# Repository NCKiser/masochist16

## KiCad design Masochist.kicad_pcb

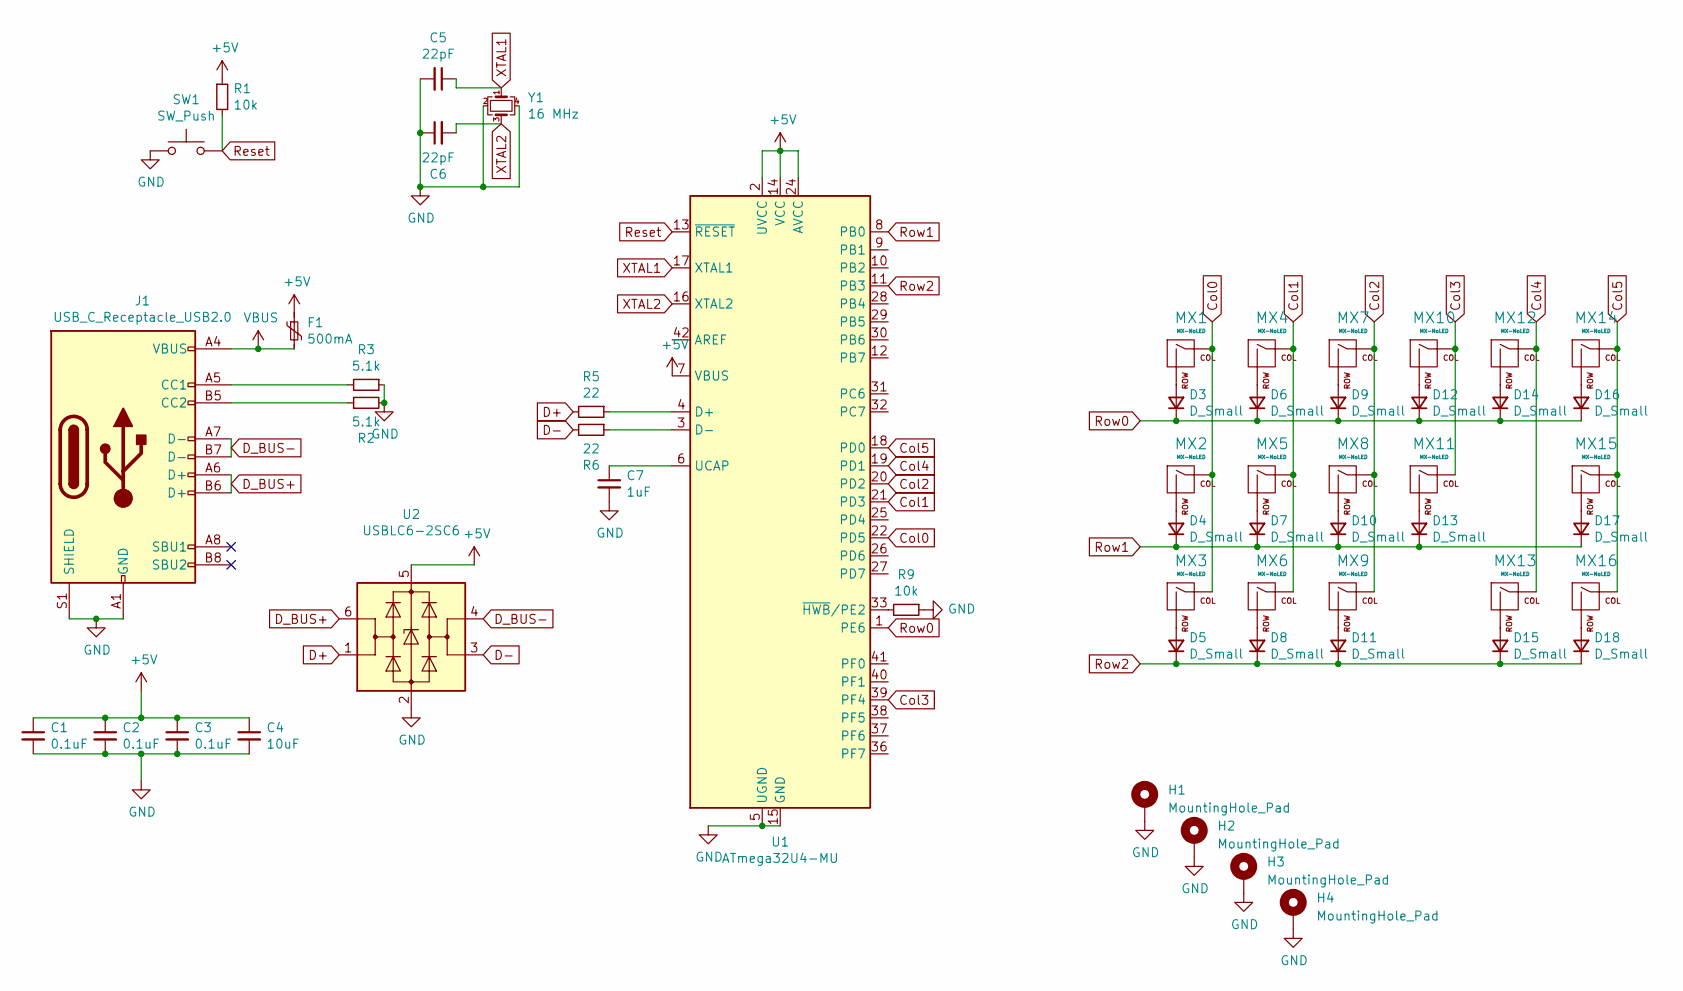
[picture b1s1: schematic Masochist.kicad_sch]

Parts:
C1, C2, C3: 0.1uF; C_0805_2012Metric
C4: 10uF; C_0805_2012Metric
C5, C6: 22pF; C_0805_2012Metric
C7: 1uF; C_0402_1005Metric
D3, D4, D5, D6, D7, D8, D9, D10, D11, D12, D13, D14, D15, D16, D17, D18: D_Small; D_SOD-123
F1: 500mA; Fuse_1206_3216Metric
H1, H2, H3, H4: MountingHole_Pad; MountingHole_2.2mm_M2_Pad
J1: USB_C_Receptacle_USB2.0; USB_C_Receptacle_XKB_U262-16XN-4BVC11
MX1, MX3, MX4, MX5, MX6, MX7, MX8, MX10, MX11, MX12, MX13, MX14, MX16: MX-NoLED; MXOnly-1U-NoLED
MX2: MX-NoLED; MXOnly-1.25U-NoLED
MX9: MX-NoLED; MXOnly-2U-ReversedStabilizers-NoLED
MX15: MX-NoLED; MXOnly-1.75U-NoLED
R1, R9: 10k; R_0805_2012Metric
R2, R3: 5.1k; R_0805_2012Metric
R5, R6: 22; R_0805_2012Metric
SW1: SW_Push; SKQG-1155865
U1: ATmega32U4-MU; QFN-44-1EP_7x7mm_P0.5mm_EP5.2x5.2mm
U2: USBLC6-2SC6; SOT-23-6
Y1: 16 MHz; Crystal_SMD_3225-4Pin_3.2x2.5mm

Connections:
+5V: C1.1, C2.1, C3.1, C4.1, F1.1, R1.1, U1.2 (UVCC), U1.7 (VBUS), U1.14 (VCC), U1.24 (AVCC), U1.34 (VCC), U1.44 (AVCC), U2.5 (VBUS)
Col0: MX1.1 (COL), MX2.1 (COL), MX3.1 (COL), U1.22 (PD5)
Col1: MX4.1 (COL), MX5.1 (COL), MX6.1 (COL), U1.21 (PD3)
Col2: MX7.1 (COL), MX8.1 (COL), MX9.1 (COL), U1.20 (PD2)
Col3: MX10.1 (COL), MX11.1 (COL), U1.39 (PF4)
Col4: MX12.1 (COL), MX13.1 (COL), U1.19 (PD1)
Col5: MX14.1 (COL), MX15.1 (COL), MX16.1 (COL), U1.18 (PD0)
D+: R5.2, U2.1 (I/O1)
D-: R6.2, U2.3 (I/O2)
D_BUS+: J1.A6 (D+), J1.B6 (D+), U2.6 (I/O1)
D_BUS-: J1.A7 (D-), J1.B7 (D-), U2.4 (I/O2)
GND: C1.2, C2.2, C3.2, C4.2, C5.2, C6.1, C7.2, H1.1, H2.1, H3.1, H4.1, J1.A1 (GND), J1.A12 (GND), J1.B1 (GND), J1.B12 (GND), J1.S1 (SHIELD), R2.2, R3.1, R9.1, SW1.1, U1.5 (UGND), U1.15 (GND), U1.23 (GND), U1.35 (GND), U1.43 (GND), U1.45 (GND), U2.2 (GND), Y1.2, Y1.4
unnamed: D3.2 (A), MX1.2 (ROW)
unnamed: D4.2 (A), MX2.2 (ROW)
unnamed: D5.2 (A), MX3.2 (ROW)
unnamed: D6.2 (A), MX4.2 (ROW)
unnamed: D7.2 (A), MX5.2 (ROW)
unnamed: D8.2 (A), MX6.2 (ROW)
unnamed: D9.2 (A), MX7.2 (ROW)
unnamed: D10.2 (A), MX8.2 (ROW)
unnamed: D11.2 (A), MX9.2 (ROW)
unnamed: D12.2 (A), MX10.2 (ROW)
unnamed: D13.2 (A), MX11.2 (ROW)
unnamed: D14.2 (A), MX12.2 (ROW)
unnamed: D15.2 (A), MX13.2 (ROW)
unnamed: D16.2 (A), MX14.2 (ROW)
unnamed: D17.2 (A), MX15.2 (ROW)
unnamed: D18.2 (A), MX16.2 (ROW)
unnamed: J1.A5 (CC1), R3.2
unnamed: J1.B5 (CC2), R2.1
unnamed: R5.1, U1.4 (D+)
unnamed: R6.1, U1.3 (D-)
unnamed: C7.1, U1.6 (UCAP)
unnamed: R9.2, U1.33 (~HWB/PE2)
Reset: R1.2, SW1.2, U1.13 (~RESET)
Row0: D3.1 (K), D6.1 (K), D9.1 (K), D12.1 (K), D14.1 (K), D16.1 (K), U1.1 (PE6)
Row1: D4.1 (K), D7.1 (K), D10.1 (K), D13.1 (K), D17.1 (K), U1.8 (PB0)
Row2: D5.1 (K), D8.1 (K), D11.1 (K), D15.1 (K), D18.1 (K), U1.11 (PB3)
VBUS: F1.2, J1.A4 (VBUS), J1.A9 (VBUS), J1.B4 (VBUS), J1.B9 (VBUS)
XTAL1: C5.1, U1.17 (XTAL1), Y1.1
XTAL2: C6.2, U1.16 (XTAL2), Y1.3

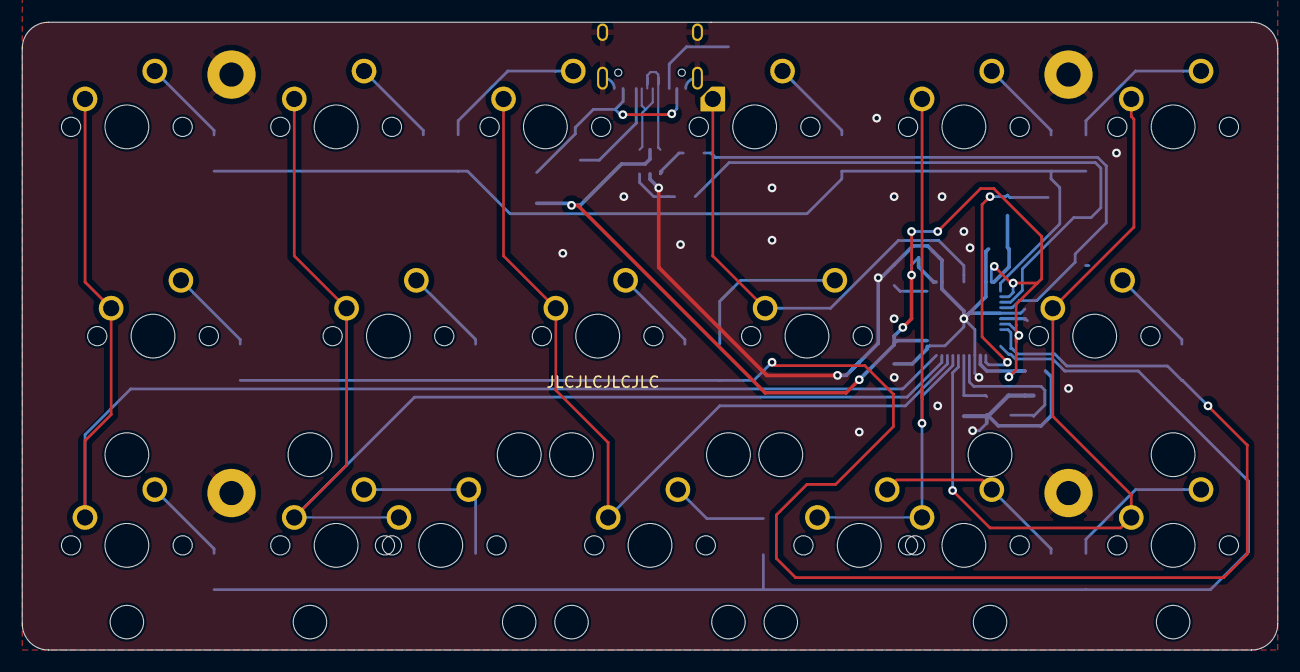
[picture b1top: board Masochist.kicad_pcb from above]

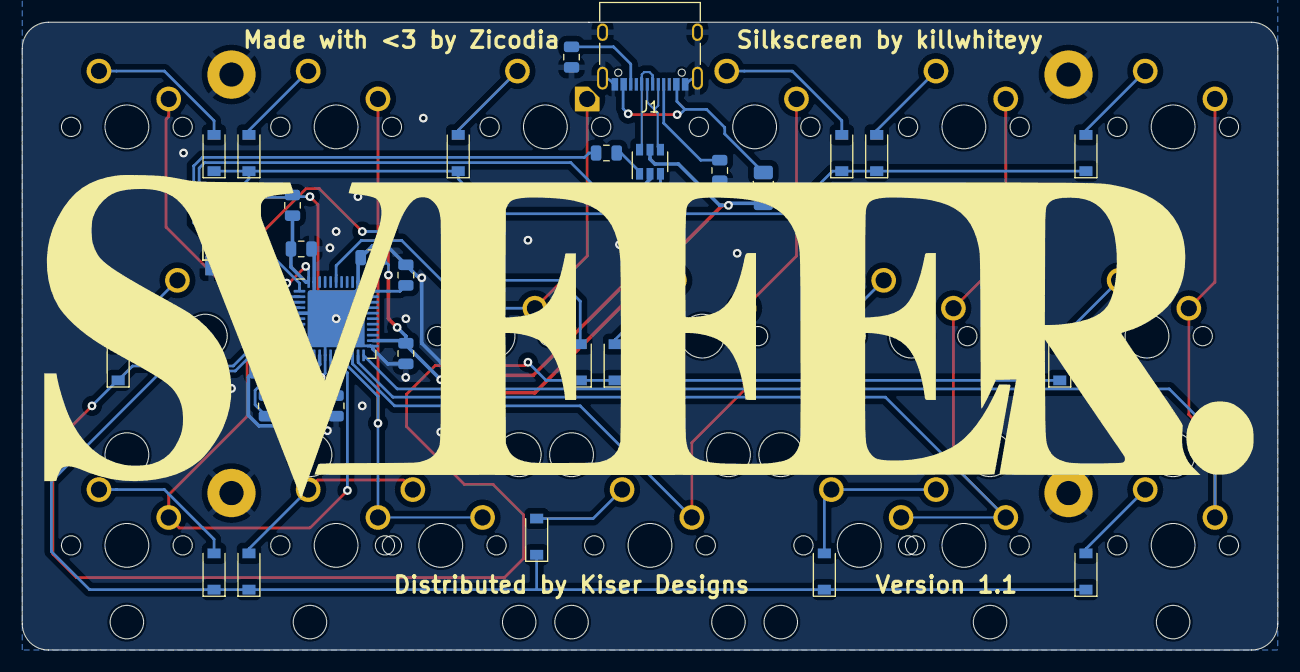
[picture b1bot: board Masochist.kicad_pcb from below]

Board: 2 copper layers, 114.3 x 57.2 mm, 58 parts (35 on the bottom side), 41 nets.

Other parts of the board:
MX6#2, MX13#2: MX-NoLED; MXOnly-2U-ReversedStabilizers-NoLED
MX9#2: MX-NoLED; STAB_MX_6u

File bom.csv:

Designator,Footprint,Quantity,Value,LCSC Part #
"C1, C2, C3",805,3,0.1uF,C1790
C4,805,1,10uF,C15850
"C5, C6",805,2,22pF,C1804
C7,504,1,1uF,C15849 
"D10, D11, D12, D13, D14, D15, D16, D17, D18, D3, D4, D5, D6, D7, D8, D9",D_SOD-123,16,D_Small,C81598
F1,1206,1,500mA,C70077
J1,USB_C_Receptacle_XKB_U262-16XN-4BVC11,1,USB_C_Receptacle_USB2.0,C319148
"R1, R9",805,2,10k,C17414
"R2, R3",805,2,5.1k,C27834
"R5, R6",805,2,22,C17561
SW1,SKQG-1155865,1,SW_Push,C2762971
U1,QFN-44-1EP_7x7mm_P0.5mm_EP5.2x5.2mm,1,ATmega32U4-MU,C112161
U2,SOT-23-6,1,USBLC6-2SC6,C2687116
Y1,Crystal_SMD_3225-4Pin_3.2x2.5mm,1,16 MHz,C13738

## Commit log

2023-05-29 add silkscreen and distribution credits
2023-07-27 add production files
2023-07-31 add case.step
2023-10-24 add v1.1
2023-10-24 adjusted LED positions
